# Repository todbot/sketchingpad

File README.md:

# SketchingPad - 20-key BLE touch pad macropad

## Features

* 20-pad capacitive touch surface with 20 SK6812 addressable LEDs backlighting the touchpads
* [XIAO nRF52840](https://wiki.seeedstudio.com/XIAO_BLE/) BLE w/ LiPo charging
* LiPo battery jack with power switch (power switch must be ON to charge)
* Tact switch to switch modes, wake up, or go into deep sleep
* Audio out jack for audio fun

## Software

Install pre-built apps using the 
**-| [sketchingpad web flasher](https://todbot.github.io/sketchingpad/) |-**

### Arduino

Most of the apps are Arduino sketches, see [`arduino/README.md`](./arduino/README.md) 
for details on Arduino firmware options including: how to flash, how to build, 
the touch layer, the BLE LED animation packet layer, 
the power tiers, etc. Examples of what's available:

* `sketchingpad_party`    -- record an animation, broadcast it, with power tiers
* `sketchingpad_midi_simple` -- USB + BLE MIDI controller
* `sketchingpad_gamepad`  -- USB + BLE HID gamepad, two sticks, D-pad, 8 buttons
* `ble_keyboard`          -- BLE HID keyboard, with power tiers
* `ble_keyboard_simple`   -- BLE HID keyboard, no power mgmt
* `hwtest_leds`           -- chases one pixel around the 20 LEDs
* `hwtest_touch_lowpower` -- pad -> LED, fading, plus three power tiers, no BLE
* `hwtest_touch`          -- pad -> LED with a fading trail, no BLE

more sketches in [arduino/README.md](./arduino/README.md).

`arduino/tests/` holds host-native tests for the dependency-free
headers: `cd arduino/tests && make run`.

### CircuitPython

CircuitPython is much easier to work with, but can't get the same low-power
modes available in Arduino. 

Each program directory holds the files to copy to the CIRCUITPY root.

* `sketchingpad_midi_simple` -- USB + BLE MIDI controller
* `ble_keyboard_lowpower` -- low-power BLE HID keyboard, 
   two power tiers rather than the Arduino sketch's three. 

These work on both versions of the board (TS20 & MPR121). 
Other programs listed in [circuitpython/README.md](./circuitpython/README.md)

Host tests for the touch layer, needing no board and no install:
`cd circuitpython/tests && make run`. They also pin the pad tables in
`touch.py` against `arduino/shared/touch_map.h`, which nothing else does.

Libraries come from circup; see `circuitpython/requirements.txt`.
See `circuitpython/notes-lowpower.md` for why only two power tiers and not three.

### Other

`docs/hardware-notes.md` is the board side: both touch chips, their pad
numbering, their INT lines, and the board changes the firmware assumes.
`docs/` also holds `low-power-notes.md` and the touch-chip datasheets.

## Hardware Design

The goal was to create a small 20 captouch pad keyboard-like board that let people 
in the same room share color patterns they "draw" on the pads, wirelessly, 
but then also could be something useful after the Sketching conference.
Also desired was that the whole PCB being low-complexity and inexpensive, 
using JLC SMD PCBA capabilities and light hand-soldering. 

The design points then:

- Small : XIAO/QTpy-format or "Supermini"-format MCU board 
- Wireless: NRF52 or ESP32 class board for WiFi/BLE 
- Low-power: NRF52 (ESP32 has 10x idle power draw and nRF can hit microamp SLEEP)
- Battery: LiPo charger or 1.5V boost converter. 1.5V boost too inefficient, 
  so LiPo charger, built-in to SuperMini and some XIAO-format boards. 
- Touch sensing: I2C touch sensor chip with 20+ electrodes and INT pin support, 
  and low quiescent current
- LEDs: backlit touchpads, not cutout

Decisions:

- MCU: **XIAO NRF52840** - BLE and built-in LiPo charging in 1" sq package.
  Runner up: NRF52840 SuperMini (nice!nano clones), but suspect build quality.
  By going with XIAO/QTPy-format boards, other similar boards could be used, 
  at the expense of the battery connections (which are in a non-standard location)
  for USB-only uses. 

- Touch chip: **TS20** - cheap on LCSC and was always in stock, except during
  final production, so a quick switch to **2x MPR121**. Both had 100 uA idle current
  and less in sleep mode but don't use sleep mode yet.
  
- LEDs: **SK6812-SIDE-A** to backlight the touchpads. Backlight through PCB costs
  power, using Neopixel-like LEDs costs power (but these are static 0.25mA/LED). 
  Using Neopixel-like LEDs on a battery-conscious design is foolish, but after
  spending weeks attempting to route an IS31FL3731 RGB design, I punted.
  The LEDs do at least have a PFET gating the power so we can save 5mA when
  not actively driving the LEDs.
  
- Battery: **LiPo 3.7V** w/ JST 2.0 mm connector (RC standard, not adafruit standard),
  using LiPo charger built-in to XIAO NRF52840. Turns out AAA in a holder is very tall! 
  I want this project to be flat. A small [3d-printable JST 2mm removal tool](https://makerworld.com/en/models/1473368-disconnect-tool-for-ph2-0-and-sh1-0-connectors#profileId-1537598) 
  is really handy.

## Enclosure

As seen in the photos, there is a simple [3d-printable enclosure](./enclosure). 
It's fast to print and you can snap the PCB in to quickly get started,
or use M2.5 screws and nuts to secure the PCB more permanently.

**Battery note:** if you have a battery, attach the it with double-sided tape to the PCB 
and install the combined assembly in the case. 

**Installation into case:** The snaps are on the top and the bottom.  
To fit the PCB, secure it under the lower snap first, 
then rotate the PCB down until it snaps with the top snaps.

**Removal of the case:** To remove the PCB from the case, 
carefully pry the top of the PCB away, working slowly on each side. 
Use the cutout holes for the button and audio jack as a place to start. 

See the [Demos](#demos) section below for a video of installation & removal.

## Pinout

The `sketchingpad1` and `sketchingpad1_mpr1` boards have the same pinout:

| Signal      | XIAO pin | Notes                         |
|-------------|----------|-------------------------------|
| `PWM_AUDIO` | D0 / A0  | to audio jack via RC filter   |
| `BUTTON`    | D10/MOSI | SW1 to GND, internal pull-up  |
| `TOUCH_INT` | D3 / A3  | open collector, R1 pulls up   |
| `SDA`       | D4       | `Wire` default                |
| `SCL`       | D5       | `Wire` default                |
| `LED_DAT`   | D6 / TX  | Neopixel data                 |
| `LED_POWER` | D7 / RX  | PFET gate, LOW = LED rail on  |

Unused pins: D1 / A1, D8 / SCK, D9 / MISO.

Note for battery power, you need to solder the BAT+ / BAT- pins on the bottom
of the XIAO to the corresponding pads on the PCB. 

## Schematics

There are two versions of the board:

- `sketchingpad1` - uses one TS20 touch chip
- `sketchingpad1_mpr` - uses two MPR121 touch chips

KiCad source files available in the "schematics" directory. 

### sketchingpad1  (TS20)

### sketchingpad1-mpr  (2xMPR121)

## Demos

###  sketchingpad1_party demo

Sketch a color pattern with your fingers on the bottom 16 pads.
After 1.5s of pause, it transmits that pattern to all other sketchingpad1_party boards.
Top 4 pads select which colors. Each pad toggles between two colors.

https://github.com/user-attachments/assets/d27a3079-bf75-4f49-8079-a613aa76e5e4

### Case install / removal

How to install & remove the case. 

https://github.com/user-attachments/assets/99311e4a-093e-42f9-914b-14518b83df6d

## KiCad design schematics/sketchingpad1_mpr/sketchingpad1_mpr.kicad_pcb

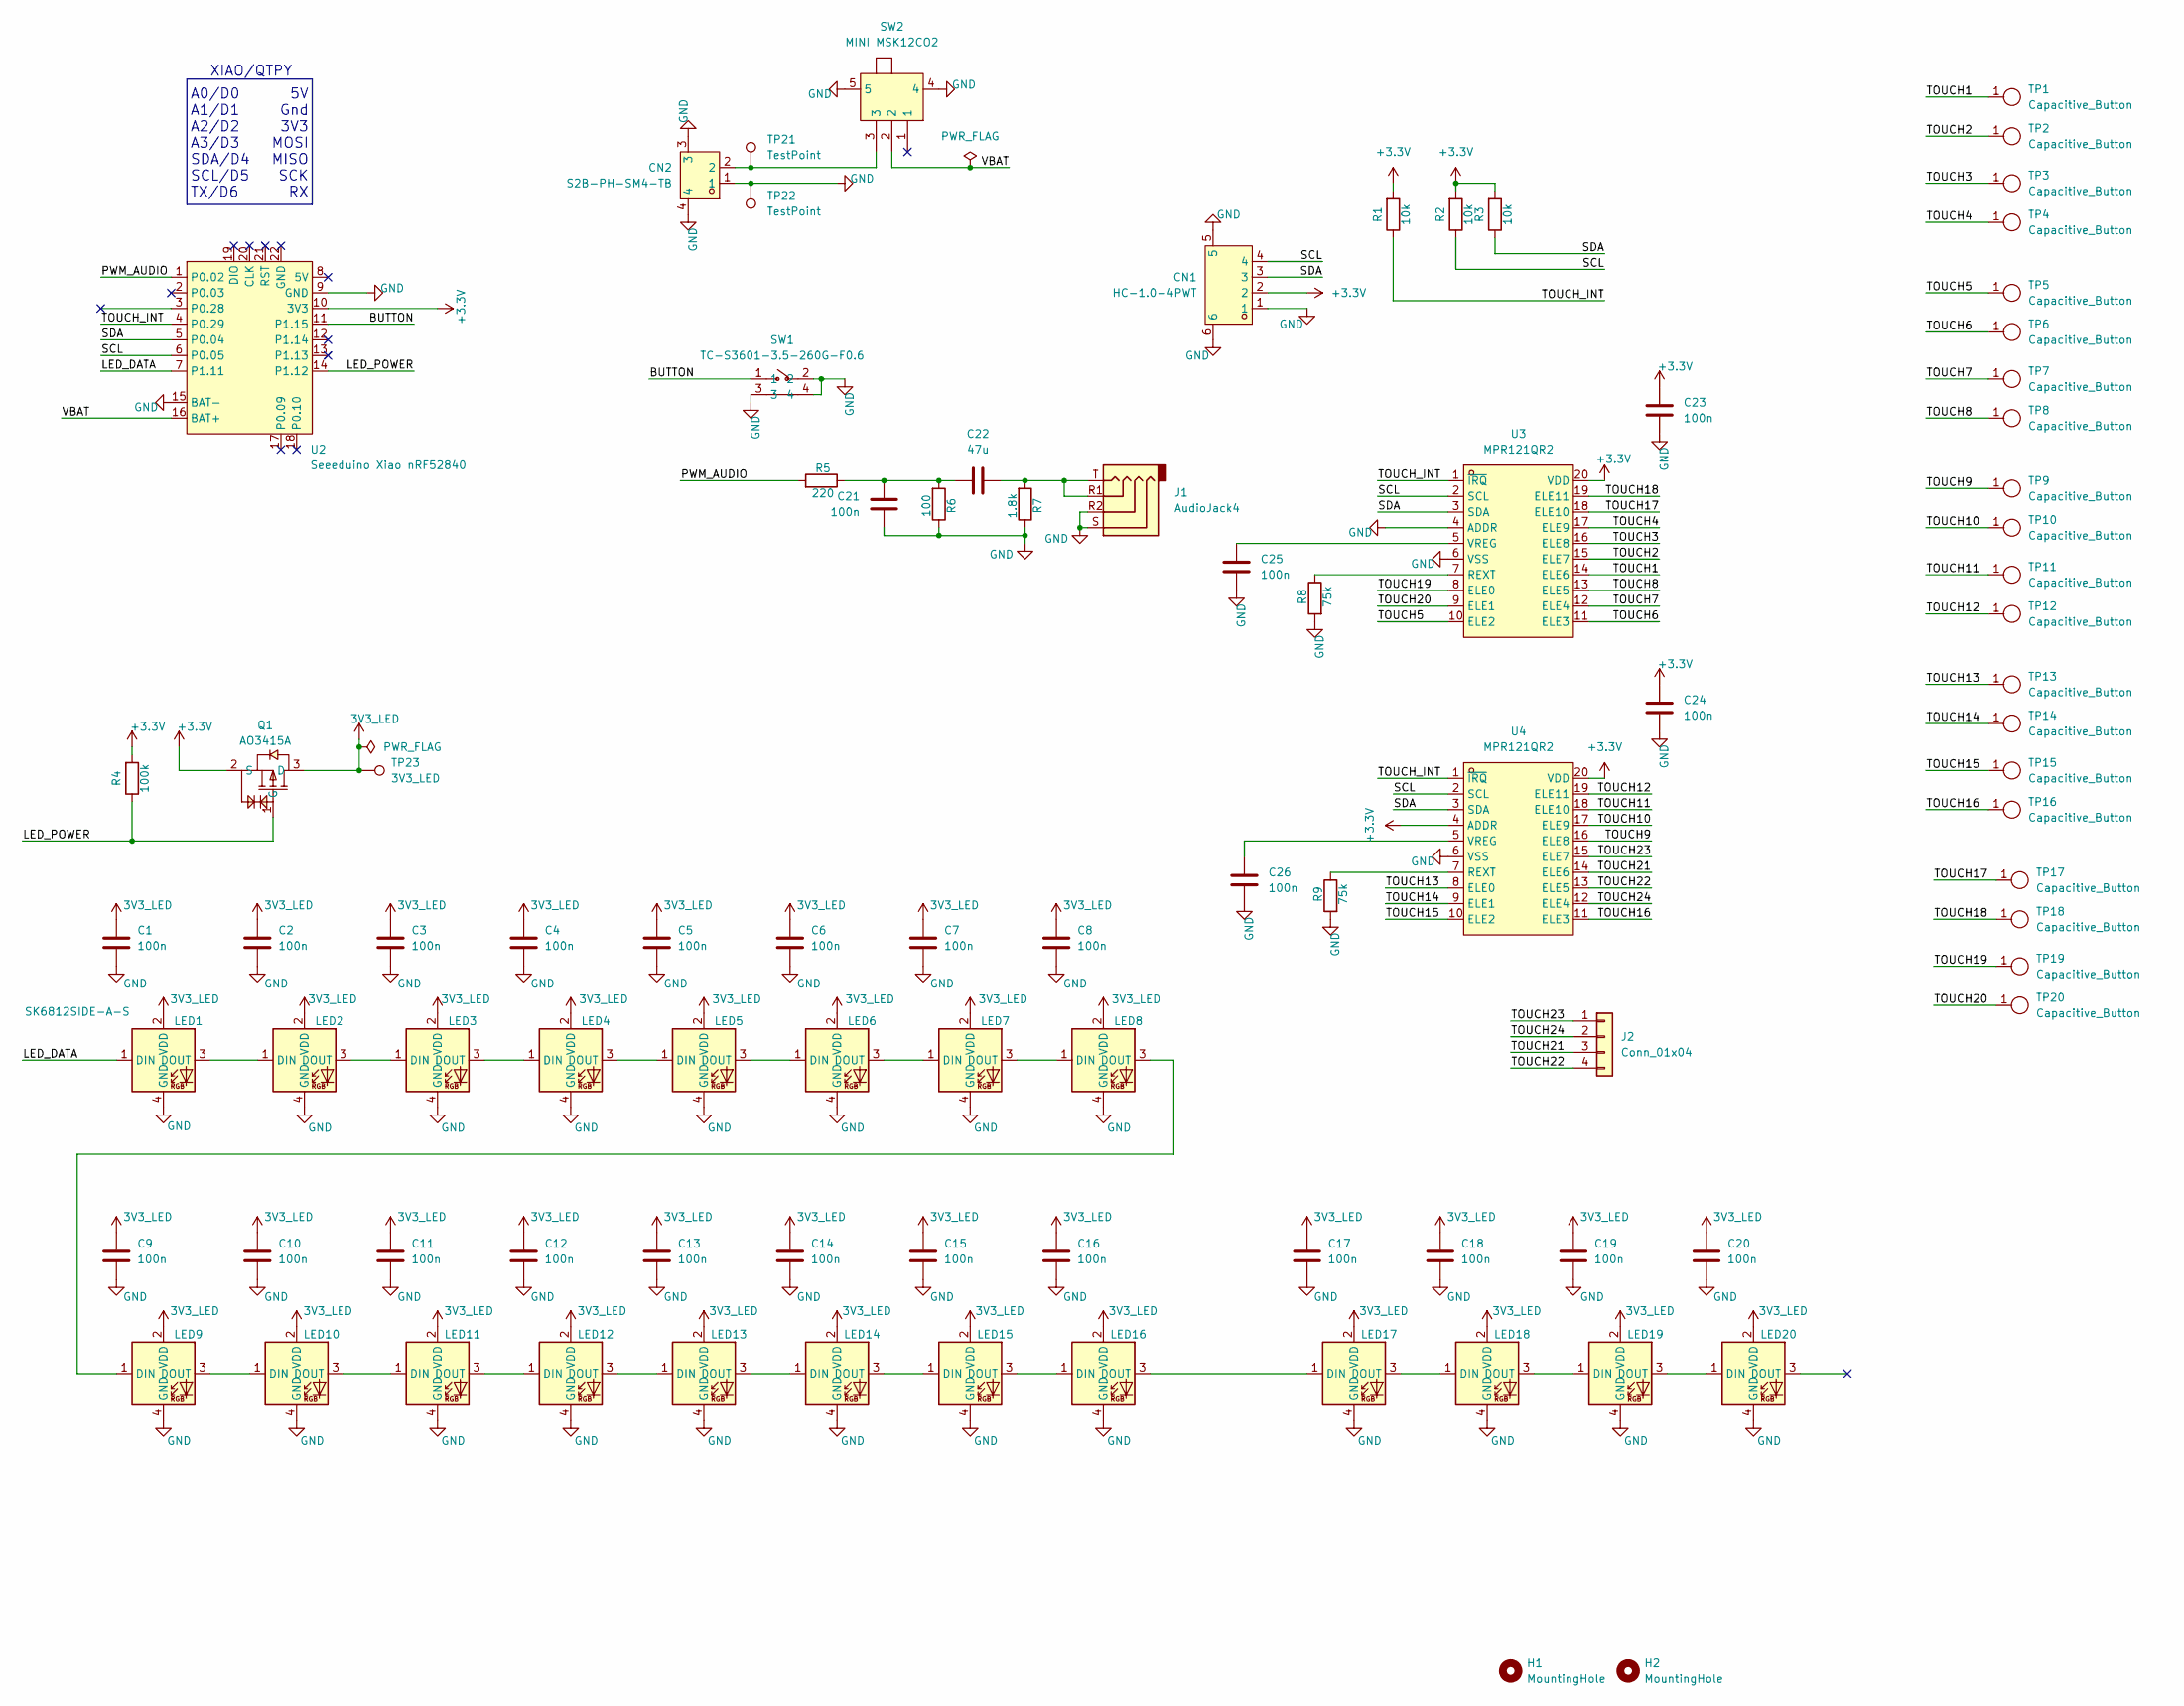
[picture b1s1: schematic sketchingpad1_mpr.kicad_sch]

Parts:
C1, C2, C3, C4, C5, C6, C7, C8, C9, C10, C11, C12, C13, C14, C15, C16, C17, C18, C19, C20, C21, C23, C24, C25, C26: 100n; C_0603_1608Metric
C22: 47u; C_0603_1608Metric
CN1: HC-1.0-4PWT; CONN-SMD_4P-P1.00_HCTL_HC-1.0-4PWT; MPN HC-1.0-4PWT; LCSC Part C2845363
CN2: S2B-PH-SM4-TB; CONN-SMD_P2.00_S2B-PH-SM4-TB-LF-SN; MPN S2B-PH-SM4-TB(LF)(SN); LCSC Part C295747
H1, H2: MountingHole; MountingHole_3mm
J1: AudioJack4; Jack_3.5mm_PJ320D_Horizontal; LCSC Part C431535
J2: Conn_01x04; PinHeader_2x02_P1.27mm_Vertical
LED1, LED2, LED3, LED4, LED5, LED6, LED7, LED8, LED9, LED10, LED11, LED12, LED13, LED14, LED15, LED16, LED17, LED18, LED19, LED20: SK6812SIDE-A-S; LED-SMD_4P-L4.0-W1.6-L-todedits; MPN SK6812SIDE-A-S; LCSC Part C5378737
Q1: AO3415A; SOT-23-3_L2.9-W1.6-P1.90-LS2.8-BR; MPN AO3415A; LCSC Part C133233
R1, R2, R3: 10k; R_0603_1608Metric
R4: 100k; R_0603_1608Metric
R5: 220; R_0603_1608Metric
R6: 100; R_0603_1608Metric
R7: 1.8k; R_0603_1608Metric
R8, R9: 75k; R_0603_1608Metric
SW1: TC-S3601-3.5-260G-F0.6; SW-SMD_TC-S3601-3.5-260G-F0.6; MPN TC-S3601-3.5-260G-F0.6; LCSC Part C49101620
SW2: MINI MSK12CO2; SW-SMD_MSK12CO2; LCSC Part C2681570
TP1, TP2, TP3, TP4, TP5, TP6, TP7, TP8, TP9, TP10, TP11, TP12, TP13, TP14, TP15, TP16, TP17, TP18, TP19, TP20: Capacitive_Button; Pad-Captouch-0.5in-backlitB
TP21, TP22: TestPoint; TestPoint_Pad_D1.5mm
TP23: 3V3_LED; TestPoint_Pad_D1.5mm
U2: Seeeduino Xiao nRF52840; Xiao_nRF52840_ACH-todedit
U3, U4: MPR121QR2; QFN-20_L3.0-W3.0-P0.40-BL; LCSC Part C91322

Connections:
3V3_LED: C1.1, C2.1, C3.1, C4.1, C5.1, C6.1, C7.1, C8.1, C9.1, C10.1, C11.1, C12.1, C13.1, C14.1, C15.1, C16.1, C17.1, C18.1, C19.1, C20.1, LED1.2 (VDD), LED2.2 (VDD), LED3.2 (VDD), LED4.2 (VDD), LED5.2 (VDD), LED6.2 (VDD), LED7.2 (VDD), LED8.2 (VDD), LED9.2 (VDD), LED10.2 (VDD), LED11.2 (VDD), LED12.2 (VDD), LED13.2 (VDD), LED14.2 (VDD), LED15.2 (VDD), LED16.2 (VDD), LED17.2 (VDD), LED18.2 (VDD), LED19.2 (VDD), LED20.2 (VDD), Q1.3 (D), TP23.1 (1_1)
+3.3V: C23.1, C24.1, CN1.2, Q1.2 (S), R1.2, R2.2, R3.2, R4.2, U2.10 (3V3), U3.20 (VDD), U4.4 (ADDR), U4.20 (VDD)
/BUTTON: SW1.1, U2.11 (P1.15)
/LED_DATA: LED1.1 (DIN), U2.7 (P1.11)
/LED_POWER: Q1.1 (G), R4.1, U2.14 (P1.12)
/PWM_AUDIO: R5.2, U2.1 (P0.02)
/SCL: CN1.4, R2.1, U2.6 (P0.05), U3.2 (SCL), U4.2 (SCL)
/SDA: CN1.3, R3.1, U2.5 (P0.04), U3.3 (SDA), U4.3 (SDA)
/TOUCH1: TP1.1 (A_1), U3.14 (ELE6)
/TOUCH2: TP2.1 (A_1), U3.15 (ELE7)
/TOUCH3: TP3.1 (A_1), U3.16 (ELE8)
/TOUCH4: TP4.1 (A_1), U3.17 (ELE9)
/TOUCH5: TP5.1 (A_1), U3.10 (ELE2)
/TOUCH6: TP6.1 (A_1), U3.11 (ELE3)
/TOUCH7: TP7.1 (A_1), U3.12 (ELE4)
/TOUCH8: TP8.1 (A_1), U3.13 (ELE5)
/TOUCH9: TP9.1 (A_1), U4.16 (ELE8)
/TOUCH10: TP10.1 (A_1), U4.17 (ELE9)
/TOUCH11: TP11.1 (A_1), U4.18 (ELE10)
/TOUCH12: TP12.1 (A_1), U4.19 (ELE11)
/TOUCH13: TP13.1 (A_1), U4.8 (ELE0)
/TOUCH14: TP14.1 (A_1), U4.9 (ELE1)
/TOUCH15: TP15.1 (A_1), U4.10 (ELE2)
/TOUCH16: TP16.1 (A_1), U4.11 (ELE3)
/TOUCH17: TP17.1 (A_1), U3.18 (ELE10)
/TOUCH18: TP18.1 (A_1), U3.19 (ELE11)
/TOUCH19: TP19.1 (A_1), U3.8 (ELE0)
/TOUCH20: TP20.1 (A_1), U3.9 (ELE1)
/TOUCH21: J2.3, U4.14 (ELE6)
/TOUCH22: J2.4, U4.13 (ELE5)
/TOUCH23: J2.1, U4.15 (ELE7)
/TOUCH24: J2.2, U4.12 (ELE4)
/TOUCH_INT: R1.1, U2.4 (P0.29), U3.1 (~IRQ), U4.1 (~IRQ)
/VBAT: SW2.2, U2.16 (BAT+)
GND: C1.2, C2.2, C3.2, C4.2, C5.2, C6.2, C7.2, C8.2, C9.2, C10.2, C11.2, C12.2, C13.2, C14.2, C15.2, C16.2, C17.2, C18.2, C19.2, C20.2, C21.2, C23.2, C24.2, C25.2, C26.2, CN1.1, CN1.5, CN1.6, CN2.1, CN2.3, CN2.4, J1.R2, J1.S, LED1.4 (GND), LED2.4 (GND), LED3.4 (GND), LED4.4 (GND), LED5.4 (GND), LED6.4 (GND), LED7.4 (GND), LED8.4 (GND), LED9.4 (GND), LED10.4 (GND), LED11.4 (GND), LED12.4 (GND), LED13.4 (GND), LED14.4 (GND), LED15.4 (GND), LED16.4 (GND), LED17.4 (GND), LED18.4 (GND), LED19.4 (GND), LED20.4 (GND), R6.1, R7.1, R8.2, R9.2, SW1.2, SW1.3, SW1.4, SW2.4, SW2.5, TP22.1 (1_1), U2.9 (GND), U2.15 (BAT-), U3.4 (ADDR), U3.6 (VSS), U4.6 (VSS)
unnamed: C21.1, C22.2, R5.1, R6.2
unnamed: C22.1, J1.R1, J1.T, R7.2
unnamed: CN2.2, SW2.3, TP21.1 (1_1)
unnamed: LED1.3 (DOUT), LED2.1 (DIN)
unnamed: LED2.3 (DOUT), LED3.1 (DIN)
unnamed: LED3.3 (DOUT), LED4.1 (DIN)
unnamed: LED4.3 (DOUT), LED5.1 (DIN)
unnamed: LED5.3 (DOUT), LED6.1 (DIN)
unnamed: LED6.3 (DOUT), LED7.1 (DIN)
unnamed: LED7.3 (DOUT), LED8.1 (DIN)
unnamed: LED8.3 (DOUT), LED9.1 (DIN)
unnamed: LED9.3 (DOUT), LED10.1 (DIN)
unnamed: LED10.3 (DOUT), LED11.1 (DIN)
unnamed: LED11.3 (DOUT), LED12.1 (DIN)
unnamed: LED12.3 (DOUT), LED13.1 (DIN)
unnamed: LED13.3 (DOUT), LED14.1 (DIN)
unnamed: LED14.3 (DOUT), LED15.1 (DIN)
unnamed: LED15.3 (DOUT), LED16.1 (DIN)
unnamed: LED16.3 (DOUT), LED17.1 (DIN)
unnamed: LED17.3 (DOUT), LED18.1 (DIN)
unnamed: LED18.3 (DOUT), LED19.1 (DIN)
unnamed: LED19.3 (DOUT), LED20.1 (DIN)
unnamed: R8.1, U3.7 (REXT)
unnamed: C25.1, U3.5 (VREG)
unnamed: R9.1, U4.7 (REXT)
unnamed: C26.1, U4.5 (VREG)

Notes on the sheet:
A0/D0 A1/D1 A2/D2 A3/D3 SDA/D4 SCL/D5 TX/D6
XIAO/QTPY
5V Gnd 3V3 MOSI MISO SCK RX

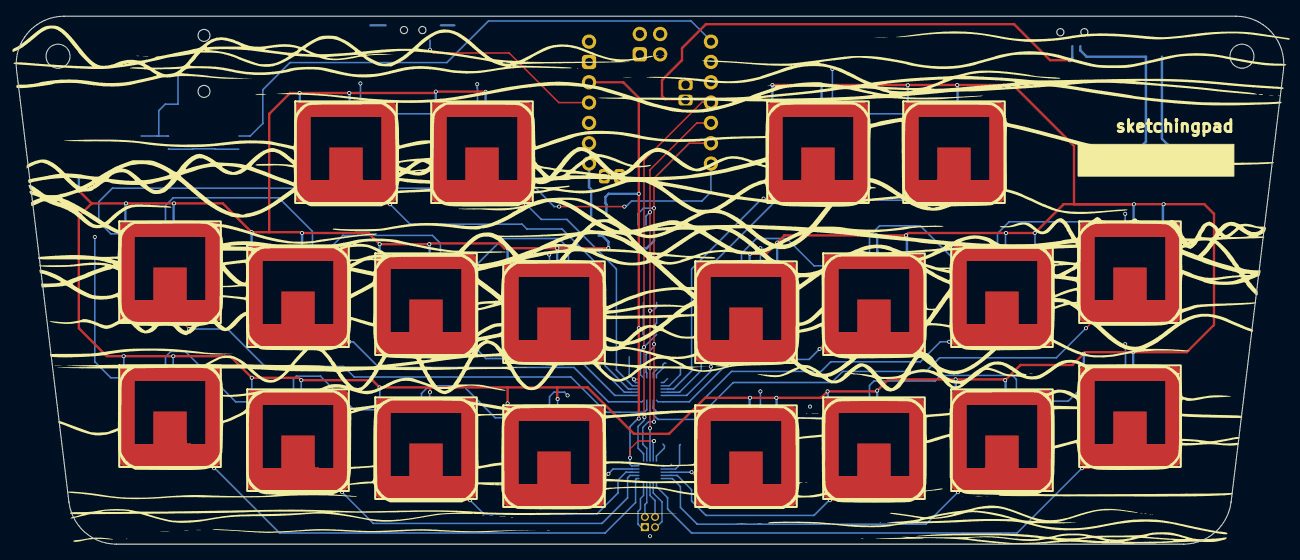
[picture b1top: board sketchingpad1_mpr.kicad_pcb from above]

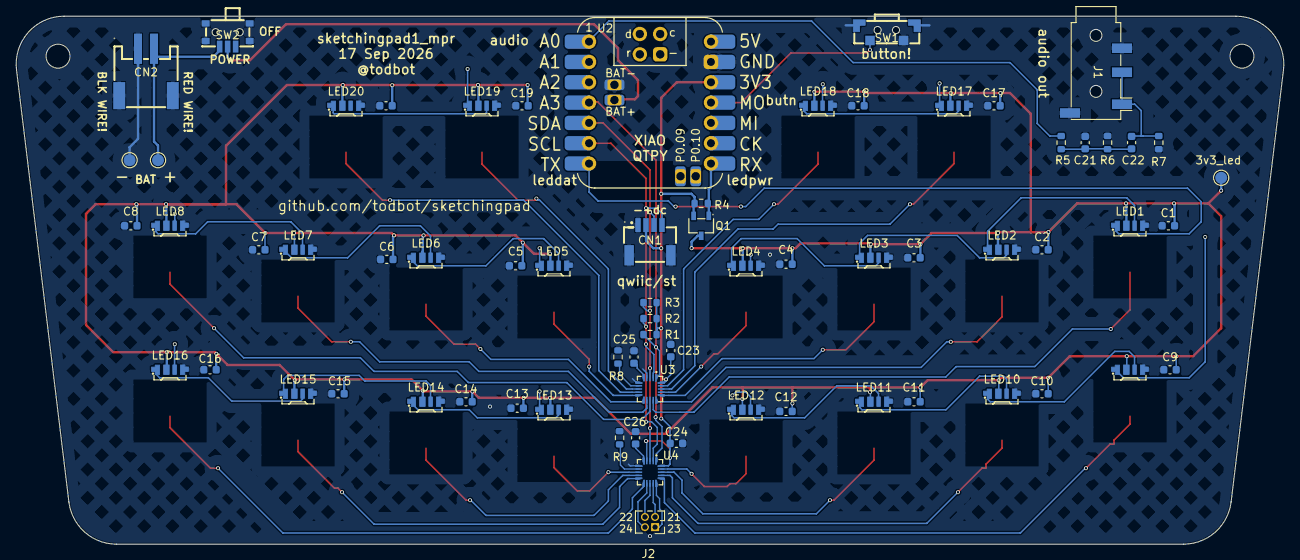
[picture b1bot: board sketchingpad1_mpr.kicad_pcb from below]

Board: 4 copper layers, 158.5 x 66.0 mm, 90 parts (68 on the bottom side), 61 nets.

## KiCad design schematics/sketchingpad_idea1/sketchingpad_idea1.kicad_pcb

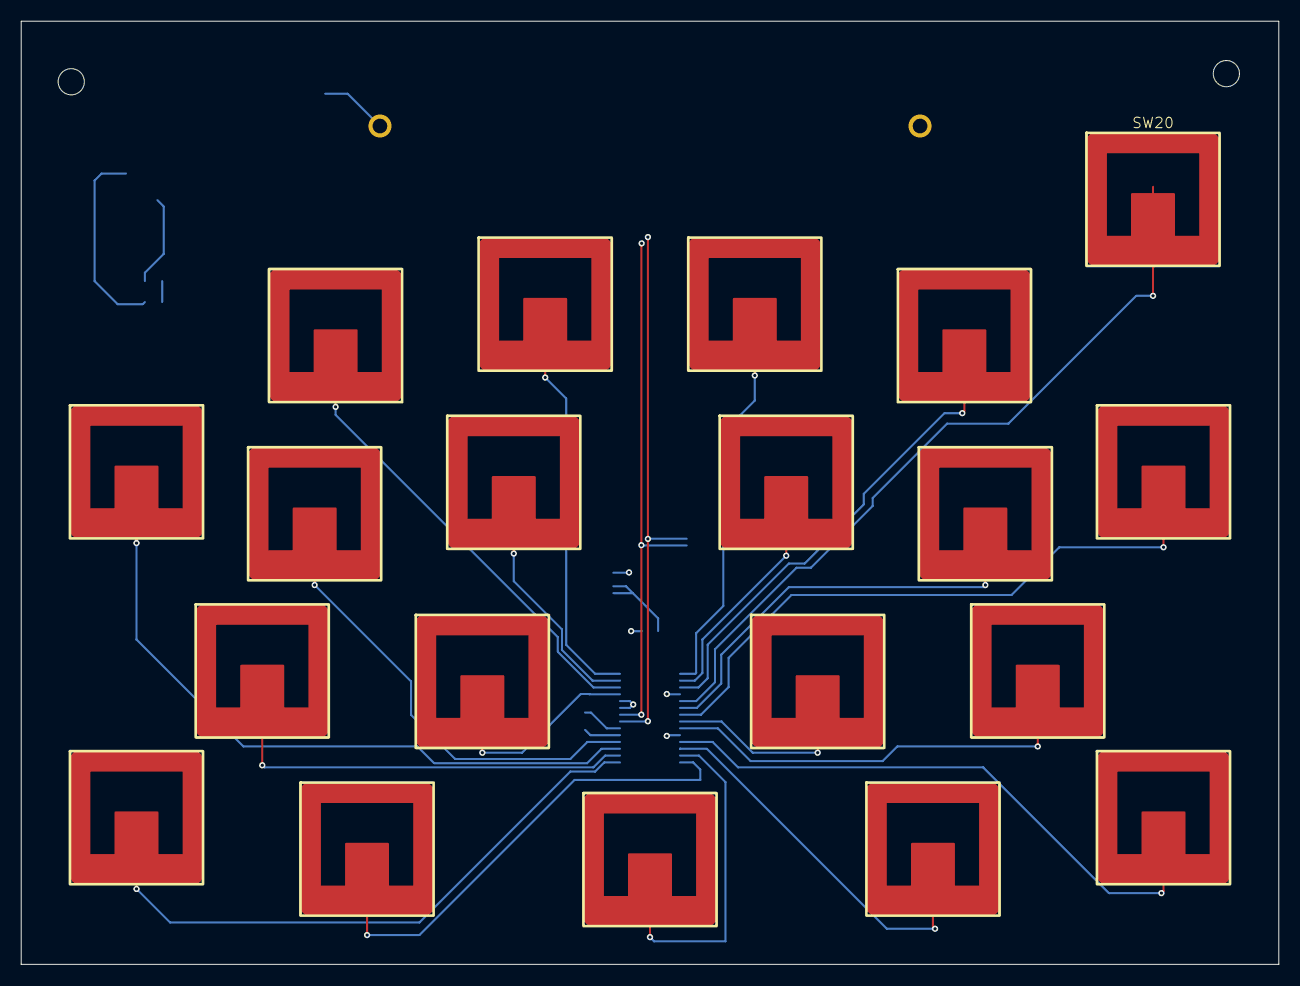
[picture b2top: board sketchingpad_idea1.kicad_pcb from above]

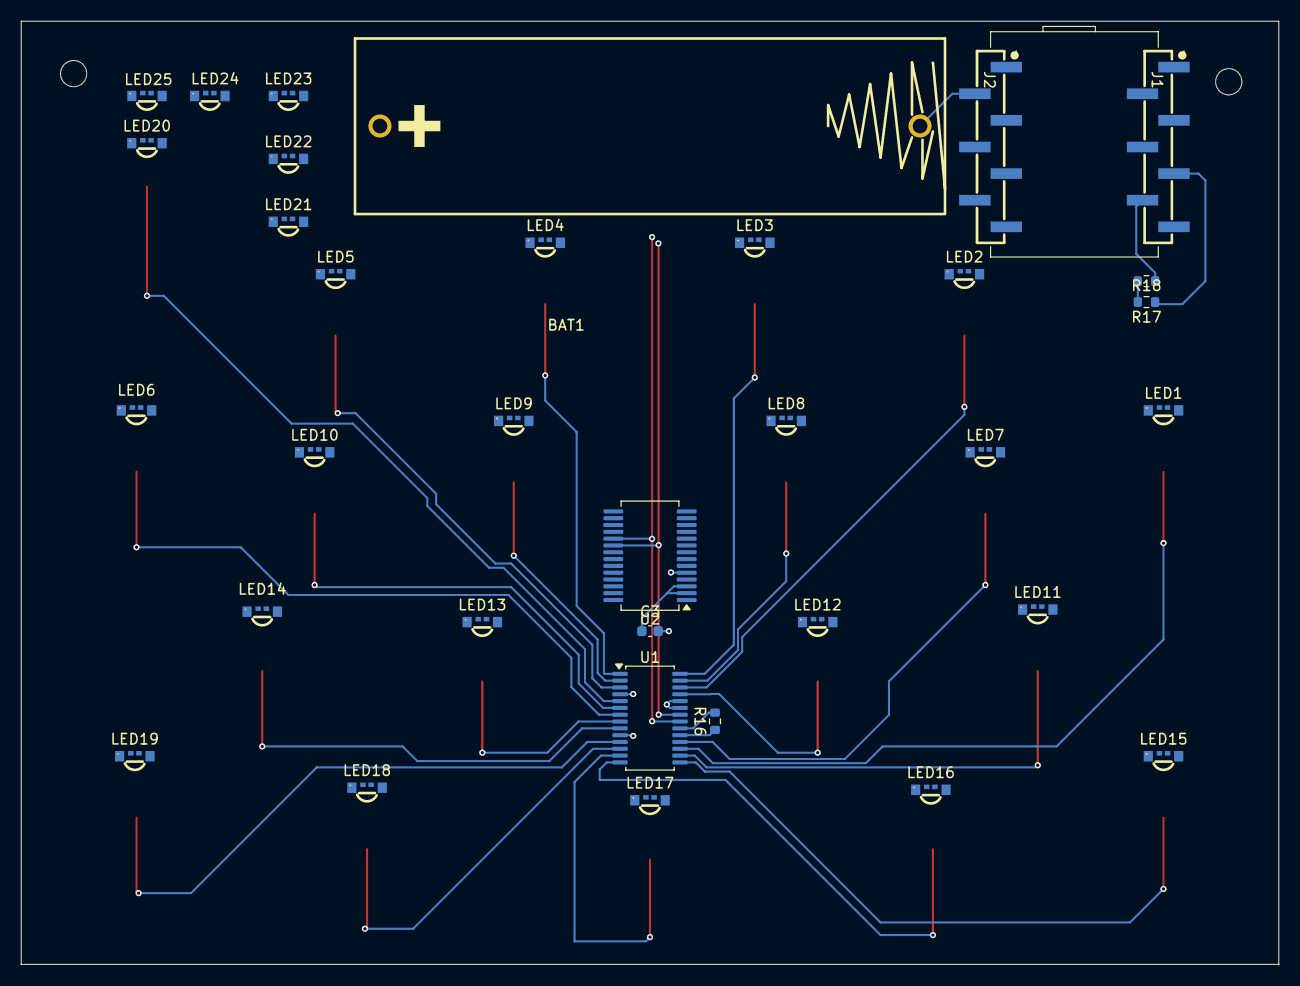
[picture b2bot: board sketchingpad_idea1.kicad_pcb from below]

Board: 4 copper layers, 120.0 x 90.0 mm, 56 parts (34 on the bottom side), 42 nets.

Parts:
BAT1: BH-AA-A1AJ020; BAT-TH_L56.3-W16.8-P51.55_BH-AA-A1AJ020
C3: 100n; C_0603_1608Metric
H1, H2: MountingHole; MountingHole_2.5mm
J1, J2: Conn_01x07; HDR-SMD_7P-P2.54_HX-PM2.54-1X7P-TP-YQ
LED1, LED2, LED3, LED4, LED5, LED6, LED7, LED8, LED9, LED10, LED11, LED12, LED13, LED14, LED15, LED16, LED17, LED18, LED19, LED20, LED21, LED22, LED23, LED24, LED25: XL-3210RGBC-YG-todclean; LED-ARRAY-SMD_HS-1204-RGB
R16, R17, R18: 10k; R_0603_1608Metric
SW1, SW2, SW3, SW4, SW5, SW6, SW7, SW8, SW9, SW10, SW11, SW12, SW13, SW14, SW15, SW16, SW17, SW18, SW19, SW20: Capacitive_Button; Pad-Captouch-0.5in-backlitB
U1: TS20; TSSOP-28_4.4x9.7mm_P0.65mm
U2: IS31FL3731-SA; SSOP-28_5.3x10.2mm_P0.65mm

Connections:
+3.3V: C3.1, J2.3, R16.2, R17.2, R18.2, U1.20 (VDD), U2.2 (VCC), U2.3 (~SDB)
/LEDs/CA1: LED1.3, LED8.3
/LEDs/CA2: LED2.3, LED3.2, LED4.2, LED5.2, LED6.2, LED7.2, LED9.3
/LEDs/CA3: LED1.2, LED2.2, LED3.3, LED4.1, LED5.1, LED6.1, LED7.1, LED10.3
/LEDs/CA4: LED1.1, LED2.1, LED3.1, LED4.3, LED11.3
/LEDs/CA5: LED5.3, LED12.3, LED13.2, LED14.2
/LEDs/CA6: LED6.3, LED8.2, LED9.2, LED10.2, LED11.2, LED12.2, LED13.3, LED14.1
/LEDs/CA7: LED7.3, LED8.1, LED9.1, LED10.1, LED11.1, LED12.1, LED13.1, LED14.3
/LEDs/CA8: LED8.4, LED9.4, LED10.4, LED11.4, LED12.4, LED13.4, LED14.4
/LEDs/CA9: LED1.4, LED2.4, LED3.4, LED4.4, LED5.4, LED6.4, LED7.4
/LEDs/CB1: LED22.4, LED23.4, LED24.4, LED25.4
/LEDs/CB2: LED16.3, LED17.2, LED18.2, LED19.2, LED20.2, LED21.2, LED23.3
/LEDs/CB3: LED15.2, LED16.2, LED17.3, LED18.1, LED19.1, LED20.1, LED21.1, LED24.3
/LEDs/CB4: LED15.1, LED16.1, LED17.1, LED18.3, LED25.3
/LEDs/CB6: LED20.3, LED22.2, LED23.2, LED24.2, LED25.2
/LEDs/CB7: LED21.3, LED22.1, LED23.1, LED24.1, LED25.1
/LEDs/CB8: LED15.4, LED16.4, LED17.4, LED18.4, LED19.4, LED20.4, LED21.4
/LEDs/CB9: LED15.3, LED22.3
/Root/SCL: J1.6, R18.1, U1.22 (SCL), U2.20 (SCL)
/Root/SDA: J1.5, R17.1, U1.21 (SDA), U2.19 (SDA)
/Root/TOUCH1: SW1.1 (A_1), U1.17 (CS19)
/Root/TOUCH2: SW2.1 (A_1), U1.26 (CS2)
/Root/TOUCH3: SW3.1 (A_1), U1.28 (CS4)
/Root/TOUCH4: SW4.1 (A_1), U1.1 (CS5)
/Root/TOUCH5: SW5.1 (A_1), U1.3 (CS7)
/Root/TOUCH6: SW6.1 (A_1), U1.7 (CS10)
/Root/TOUCH7: SW7.1 (A_1), U1.18 (CS20)
/Root/TOUCH8: SW8.1 (A_1), U1.27 (CS3)
/Root/TOUCH9: SW9.1 (A_1), U1.2 (CS6)
/Root/TOUCH10: SW10.1 (A_1), U1.6 (CS9)
/Root/TOUCH11: SW11.1 (A_1), U1.16 (CS18)
/Root/TOUCH12: SW12.1 (A_1), U1.25 (CS1)
/Root/TOUCH13: SW13.1 (A_1), U1.8 (CS11)
/Root/TOUCH14: SW14.1 (A_1), U1.9 (CS12)
/Root/TOUCH15: SW15.1 (A_1), U1.15 (CS17)
/Root/TOUCH16: SW16.1 (A_1), U1.14 (CS16)
/Root/TOUCH17: SW17.1 (A_1), U1.13 (CS15)
/Root/TOUCH18: SW18.1 (A_1), U1.12 (CS14)
/Root/TOUCH19: SW19.1 (A_1), U1.11 (CS13)
/Root/TOUCH20: SW20.1 (A_1), U1.5 (CS8)
GND: BAT1.1 (1_1), C3.2, J2.2, U1.4 (VSS), U1.10 (VSS), U1.23 (VSS), U1.24 (ADD), U2.5 (GND)
unnamed: R16.1, U1.19 (INT)

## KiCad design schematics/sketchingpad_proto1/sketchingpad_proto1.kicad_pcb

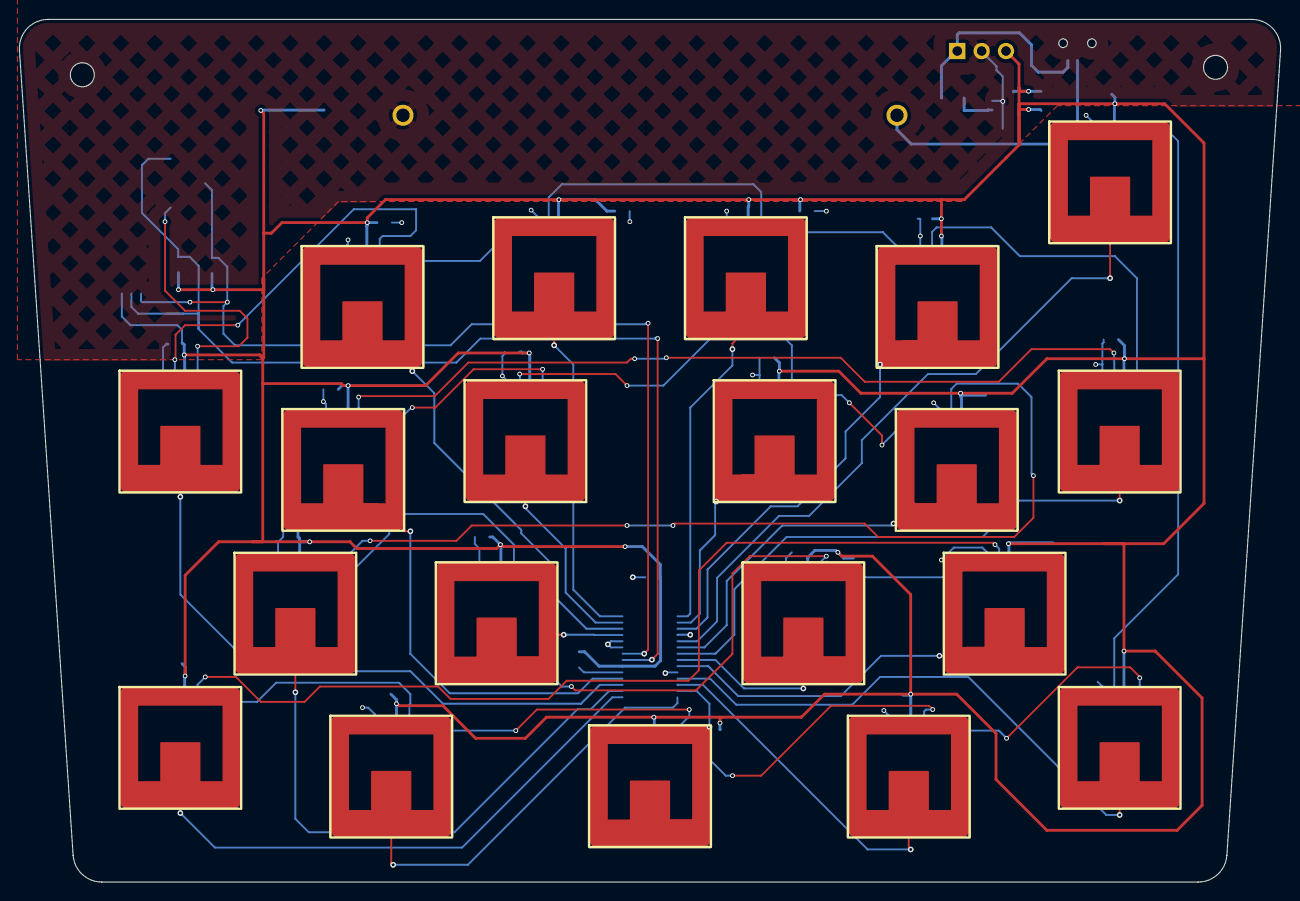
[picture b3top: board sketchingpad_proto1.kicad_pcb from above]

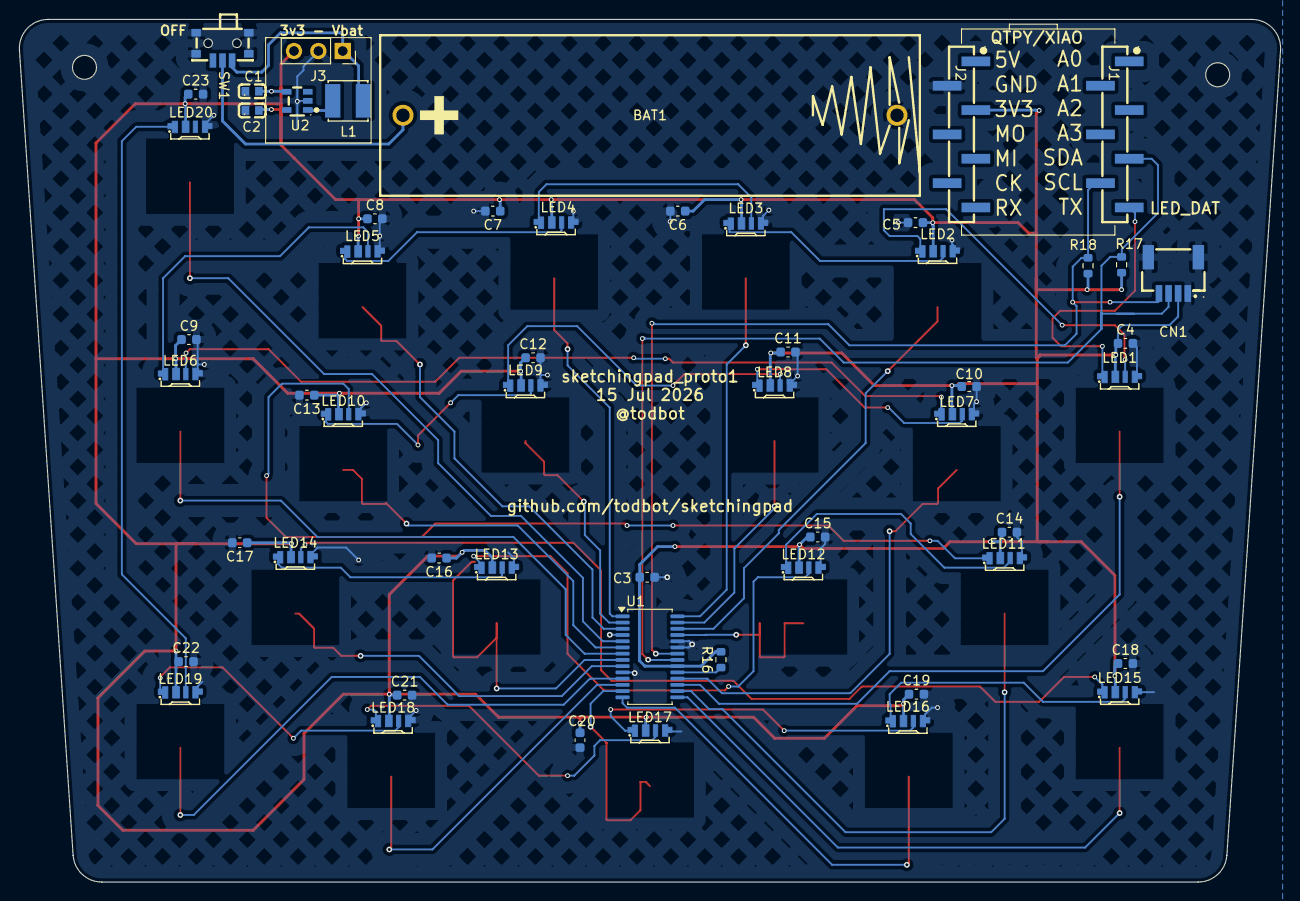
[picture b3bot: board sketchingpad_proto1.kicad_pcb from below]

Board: 4 copper layers, 131.6 x 90.0 mm, 77 parts (55 on the bottom side), 48 nets.

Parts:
BAT1: BH-AA-A1AJ020; BAT-TH_L56.3-W16.8-P51.55_BH-AA-A1AJ020
C1, C2: CL10A106KP8NNNC; C0603
C3, C4, C5, C6, C7, C8, C9, C10, C11, C12, C13, C14, C15, C16, C17, C18, C19, C20, C21, C22, C23: 100n; C_0603_1608Metric
CN1: HC-1.0-4PWT; CONN-SMD_4P-P1.00_HCTL_HC-1.0-4PWT
H1, H2: MountingHole; MountingHole_2.5mm
J1, J2: Conn_01x07; HDR-SMD_7P-P2.54_HX-PM2.54-1X7P-TP-YQ
J3: Conn_01x03; PinSocket_1x03_P2.54mm_Vertical
L1: SWPA4030S4R7MT; IND-SMD_L4.0-W4.0
LED1, LED2, LED3, LED4, LED5, LED6, LED7, LED8, LED9, LED10, LED11, LED12, LED13, LED14, LED15, LED16, LED17, LED18, LED19, LED20: SK6812SIDE-A-S; LED-SMD_4P-L4.0-W1.6-L
R16, R17, R18: 10k; R_0603_1608Metric
SW1: MINI MSK12CO2; SW-SMD_MSK12CO2
TP1, TP2, TP3, TP4, TP5, TP6, TP7, TP8, TP9, TP10, TP11, TP12, TP13, TP14, TP15, TP16, TP17, TP18, TP19, TP20: Capacitive_Button; Pad-Captouch-0.5in-backlitB
U1: TS20; TSSOP-28_4.4x9.7mm_P0.65mm
U2: TPS613221ADBVR; SOT-23-5_L2.9-W1.6-P0.95-LS2.8-BR

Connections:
+3.3V: C1.2, C2.2, C3.1, C4.1, C5.1, C6.1, C7.1, C8.1, C9.1, C10.1, C11.1, C12.1, C13.1, C14.1, C15.1, C16.1, C17.1, C18.1, C19.1, C20.1, C21.1, C22.1, C23.1, CN1.2, J2.3, J3.3, LED1.2 (VDD), LED2.2 (VDD), LED3.2 (VDD), LED4.2 (VDD), LED5.2 (VDD), LED6.2 (VDD), LED7.2 (VDD), LED8.2 (VDD), LED9.2 (VDD), LED10.2 (VDD), LED11.2 (VDD), LED12.2 (VDD), LED13.2 (VDD), LED14.2 (VDD), LED15.2 (VDD), LED16.2 (VDD), LED17.2 (VDD), LED18.2 (VDD), LED19.2 (VDD), LED20.2 (VDD), R16.2, R17.2, R18.2, U1.20 (VDD), U2.4 (VOUT)
/Root/SCL: CN1.4, J1.6, R18.1, U1.22 (SCL)
/Root/SDA: CN1.3, J1.5, R17.1, U1.21 (SDA)
/Root/TOUCH1: TP1.1 (A_1), U1.17 (CS19)
/Root/TOUCH2: TP2.1 (A_1), U1.26 (CS2)
/Root/TOUCH3: TP3.1 (A_1), U1.28 (CS4)
/Root/TOUCH4: TP4.1 (A_1), U1.1 (CS5)
/Root/TOUCH5: TP5.1 (A_1), U1.3 (CS7)
/Root/TOUCH6: TP6.1 (A_1), U1.7 (CS10)
/Root/TOUCH7: TP7.1 (A_1), U1.18 (CS20)
/Root/TOUCH8: TP8.1 (A_1), U1.27 (CS3)
/Root/TOUCH9: TP9.1 (A_1), U1.2 (CS6)
/Root/TOUCH10: TP10.1 (A_1), U1.6 (CS9)
/Root/TOUCH11: TP11.1 (A_1), U1.16 (CS18)
/Root/TOUCH12: TP12.1 (A_1), U1.25 (CS1)
/Root/TOUCH13: TP13.1 (A_1), U1.8 (CS11)
/Root/TOUCH14: TP14.1 (A_1), U1.9 (CS12)
/Root/TOUCH15: TP15.1 (A_1), U1.15 (CS17)
/Root/TOUCH16: TP16.1 (A_1), U1.14 (CS16)
/Root/TOUCH17: TP17.1 (A_1), U1.13 (CS15)
/Root/TOUCH18: TP18.1 (A_1), U1.12 (CS14)
/Root/TOUCH19: TP19.1 (A_1), U1.11 (CS13)
/Root/TOUCH20: TP20.1 (A_1), U1.5 (CS8)
/Root/VBAT: J3.1, L1.1, SW1.1
GND: BAT1.1, C1.1, C2.1, C3.2, C4.2, C5.2, C6.2, C7.2, C8.2, C9.2, C10.2, C11.2, C12.2, C13.2, C14.2, C15.2, C16.2, C17.2, C18.2, C19.2, C20.2, C21.2, C22.2, C23.2, CN1.1, CN1.5, CN1.6, J2.2, J3.2, LED1.4 (GND), LED2.4 (GND), LED3.4 (GND), LED4.4 (GND), LED5.4 (GND), LED6.4 (GND), LED7.4 (GND), LED8.4 (GND), LED9.4 (GND), LED10.4 (GND), LED11.4 (GND), LED12.4 (GND), LED13.4 (GND), LED14.4 (GND), LED15.4 (GND), LED16.4 (GND), LED17.4 (GND), LED18.4 (GND), LED19.4 (GND), LED20.4 (GND), SW1.4, SW1.5, U1.4 (VSS), U1.10 (VSS), U1.23 (VSS), U1.24 (ADD), U2.2 (GND)
LED_DAT: J1.7, LED1.1 (DIN)
unnamed: BAT1.2, SW1.2
unnamed: LED1.3 (DOUT), LED2.1 (DIN)
unnamed: LED2.3 (DOUT), LED3.1 (DIN)
unnamed: LED3.3 (DOUT), LED4.1 (DIN)
unnamed: LED4.3 (DOUT), LED5.1 (DIN)
unnamed: LED5.3 (DOUT), LED6.1 (DIN)
unnamed: LED6.3 (DOUT), LED7.1 (DIN)
unnamed: LED7.3 (DOUT), LED8.1 (DIN)
unnamed: LED8.3 (DOUT), LED9.1 (DIN)
unnamed: LED9.3 (DOUT), LED10.1 (DIN)
unnamed: LED10.3 (DOUT), LED11.1 (DIN)
unnamed: LED11.3 (DOUT), LED12.1 (DIN)
unnamed: LED12.3 (DOUT), LED13.1 (DIN)
unnamed: LED13.3 (DOUT), LED14.1 (DIN)
unnamed: LED14.3 (DOUT), LED15.1 (DIN)
unnamed: LED15.3 (DOUT), LED16.1 (DIN)
unnamed: LED16.3 (DOUT), LED17.1 (DIN)
unnamed: LED17.3 (DOUT), LED18.1 (DIN)
unnamed: LED18.3 (DOUT), LED19.1 (DIN)
unnamed: LED19.3 (DOUT), LED20.1 (DIN)
unnamed: R16.1, U1.19 (INT)
unnamed: L1.2, U2.1 (SW)

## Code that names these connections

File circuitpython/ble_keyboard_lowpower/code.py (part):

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# touch.py cover both.
PIN_SDA = board.D4
PIN_SCL = board.D5
PIN_LED_DATA = board.D6
PIN_LED_POWER = board.D7  # P-FET gate, LOW = rail on
PIN_TOUCH_INT = board.D3  # open collector, R1 pulls it up; both /IRQ on _mpr
PIN_BUTTON = board.D10  # SW1 to GND

NUM_LEDS = 20
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
# ----------------------------------------------------------------- LED rail

led_power = digitalio.DigitalInOut(PIN_LED_POWER)
led_power.switch_to_output(value=True)  # rail off until we ask for it

# Both are built and torn down by set_rail(); only one exists at a time,
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        led_power.value = False  # P-FET on
        time.sleep(0.002)
        leds = neopixel.NeoPixel(
            PIN_LED_DATA, NUM_LEDS, brightness=LED_BRIGHTNESS, auto_write=False
        )
        leds.fill(0)
        leds.show()
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        leds.show()
        leds.deinit()
        leds = None
        data_low = digitalio.DigitalInOut(PIN_LED_DATA)
        data_low.switch_to_output(value=False)
        led_power.value = True  # P-FET off (gate to source)
        rail_on = False
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
i2c = busio.I2C(PIN_SCL, PIN_SDA, frequency=400_000)

# int_pin=None because PIN_TOUCH_INT belongs to the PinAlarm below, and a
# DigitalInOut holding it would make light_sleep_until_alarms() fail.  Only
# the MPR121 path reads the line, so the TS20 board loses nothing.
#
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    # Python API calling it "level" -- which is what the TS20 needs, since
    # its INT is a ~1 ms active-low pulse rather than a held level.
    woke = alarm.light_sleep_until_alarms(
        alarm.pin.PinAlarm(PIN_TOUCH_INT, value=False, pull=False),  # R1 pulls up
        alarm.pin.PinAlarm(PIN_BUTTON, value=False, pull=True),  # SW1 to GND
        alarm.time.TimeAlarm(
            monotonic_time=time.monotonic()
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

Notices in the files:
circuitpython/ble_keyboard_lowpower/code.py:
SPDX-FileCopyrightText: 2026 Tod Kurt
SPDX-License-Identifier: GPL-3.0-or-later
